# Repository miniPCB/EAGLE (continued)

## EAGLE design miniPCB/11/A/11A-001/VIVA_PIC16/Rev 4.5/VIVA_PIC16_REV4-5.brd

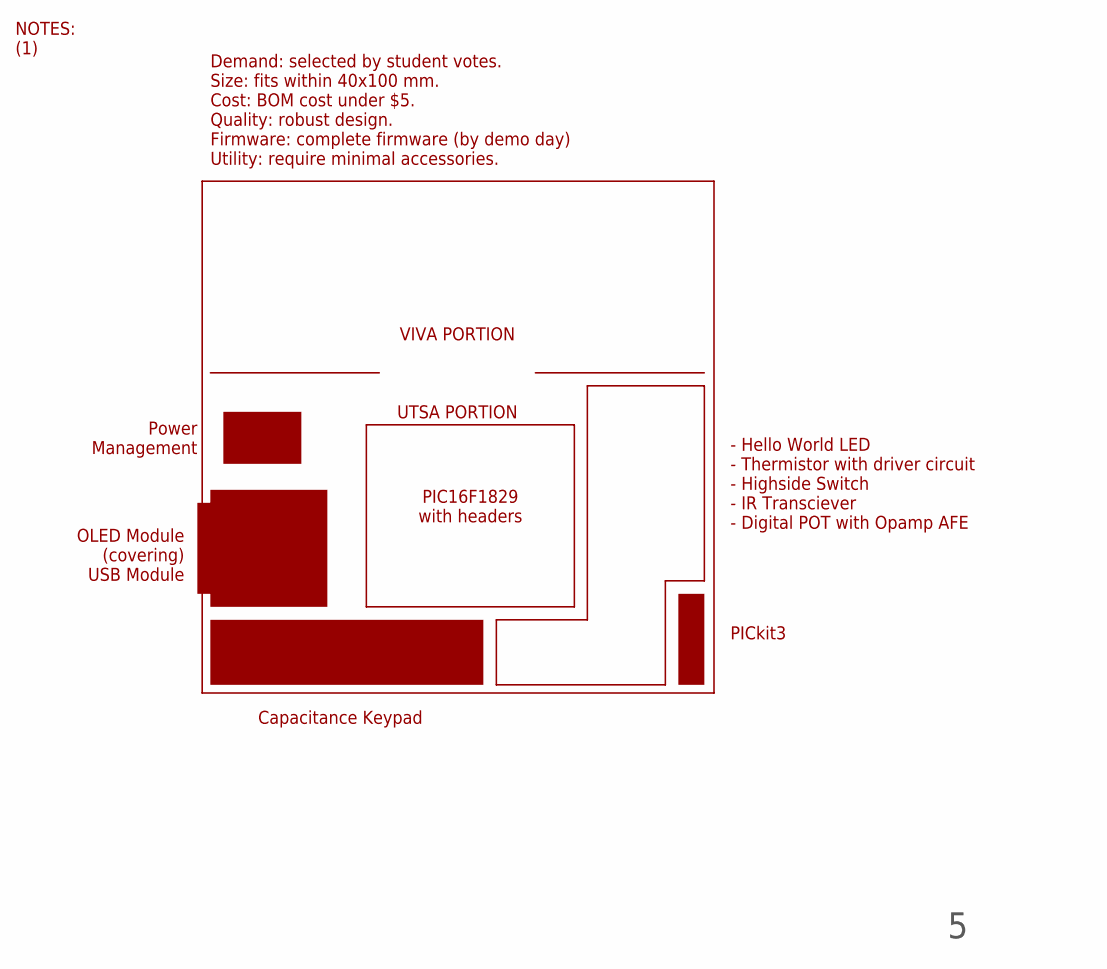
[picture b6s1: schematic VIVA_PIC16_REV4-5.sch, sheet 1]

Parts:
U$1: VIVA_LOGO

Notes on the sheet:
NOTES: (1)
UTSA PORTION
VIVA PORTION
Demand: selected by student votes. Size: fits within 40x100 mm. Cost: BOM cost under $5. Quality: robust design. Firmware: complete firmware (by demo day) Utility: require minimal accessories.
OLED Module (covering) USB Module
Power Management
Capacitance Keypad
PICkit3
PIC16F1829 with headers
- Hello World LED - Thermistor with driver circuit - Highside Switch - IR Transciever - Digital POT with Opamp AFE

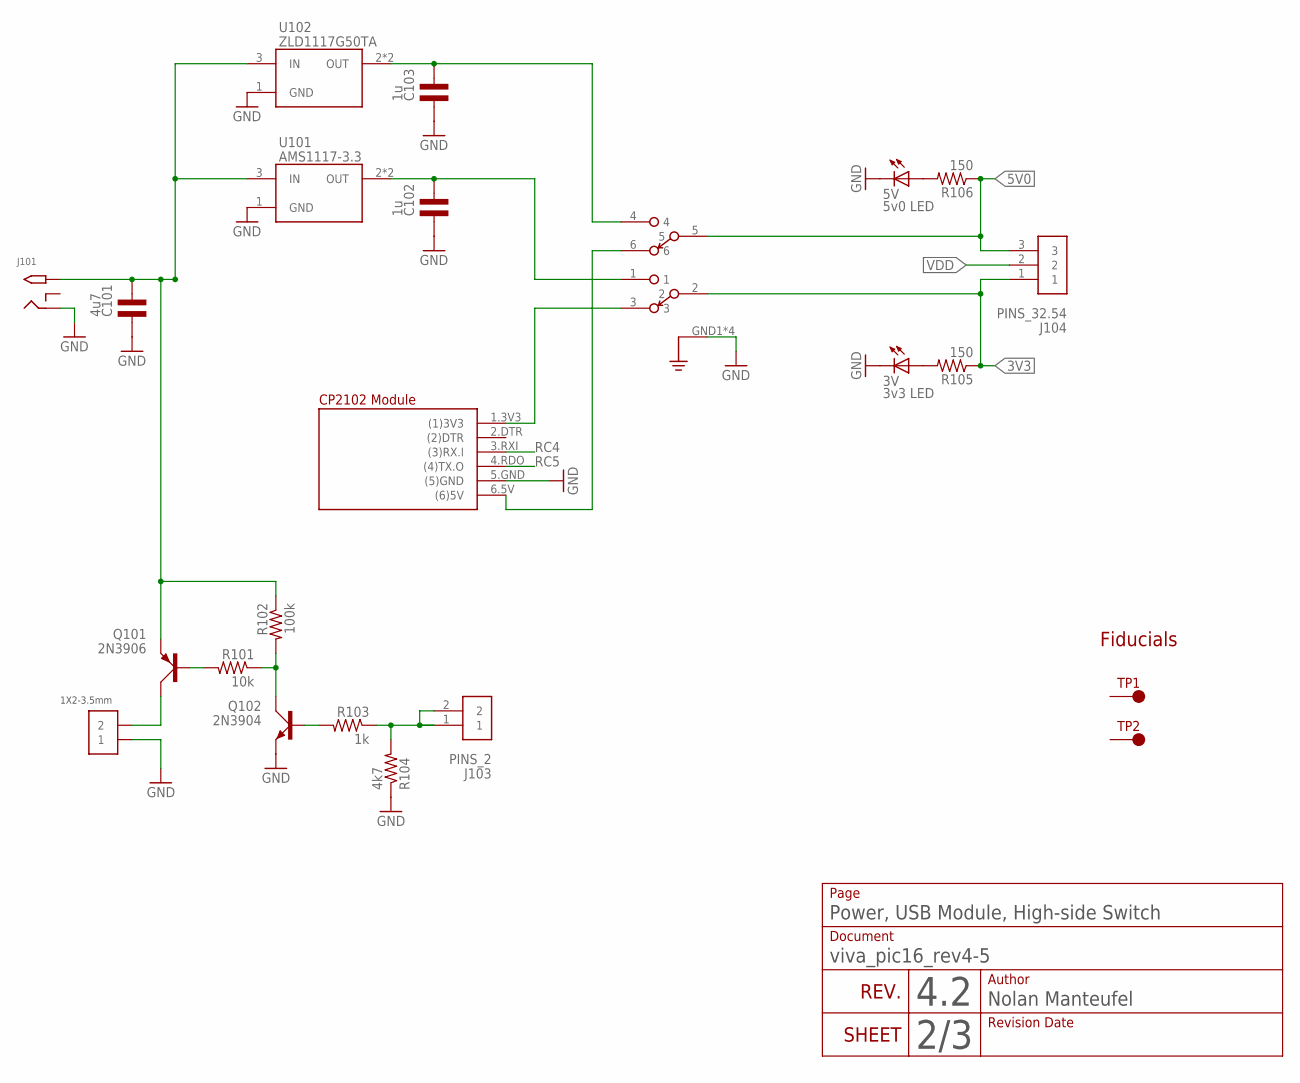
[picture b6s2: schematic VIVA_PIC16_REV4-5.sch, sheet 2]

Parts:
3V: 3v3 LED; CHIPLED_0805
5V: 5v0 LED; CHIPLED_0805
C101: 4u7; C0805
C102, C103: 1u; C0805
J101: 2.1MMJACKTHM; PJ-102A
J102: 1X2-3.5MM-3.5MM; 1X2-3.5MM
J103: PINS_2
J104: PINS_32.54; PINS_3
M101: VIVA_USB-TTL; VIVA_USB_TTL_SUBTEXT
Q101: 2N3906; SOT23
Q102: 2N3904; SOT23
R101: 10k; R0805
R102: 100k; R0805
R103: 1k; R0805
R104: 4k7; R0805
R105, R106: 150; R0805
S101: SWITCH_OS202013; OS202013MT5QN1
TP1, TP2: TESTPOINTFIDUCIAL; FIDUCIAL
U101: AMS1117-3.3; SOT223
U102: ZLD1117G50TA; SOT223

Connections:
3V3: J104.1, R105.1, S101.2
5V0: J104.3, R106.1, S101.5
GND: 3V.C, 5V.C, C101.1, C102.1, C103.1, J101.RING, J102.1, M101.5.GND ((5)GND), Q102.2 (E), R104.1, S101.GND1 (GND), S101.GND2 (GND), S101.GND3 (GND), S101.GND4 (GND), U101.1 (GND), U102.1 (GND); also elsewhere on the board
unnamed: J103.1, J103.2, R103.1, R104.2
unnamed: 5V.A, R106.2
unnamed: Q101.1 (B), R101.2
unnamed: Q102.3 (C), R101.1, R102.2
unnamed: Q102.1 (B), R103.2
unnamed: M101.1.3V3 ((1)3V3), S101.3
unnamed: J102.2, Q101.3 (C)
unnamed: M101.6.5V ((6)5V), S101.6
unnamed: C103.2, S101.4, U102.2 (OUT), U102.4.TAB (OUT)
unnamed: C102.2, S101.1, U101.2 (OUT), U101.4.TAB (OUT)
unnamed: 3V.A, R105.2
RC4: M101.3.RXI ((3)RX.I); also elsewhere on the board
RC5: M101.4.RDO ((4)TX.O); also elsewhere on the board
VDC: C101.2, J101.TIP, Q101.2 (E), R102.1, U101.3 (IN), U102.3 (IN)
VDD: J104.2; also elsewhere on the board

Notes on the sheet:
REV.
4.2
Revision Date
Author
SHEET
Document
Power, USB Module, High-side Switch
Page
Nolan Manteufel
Fiducials

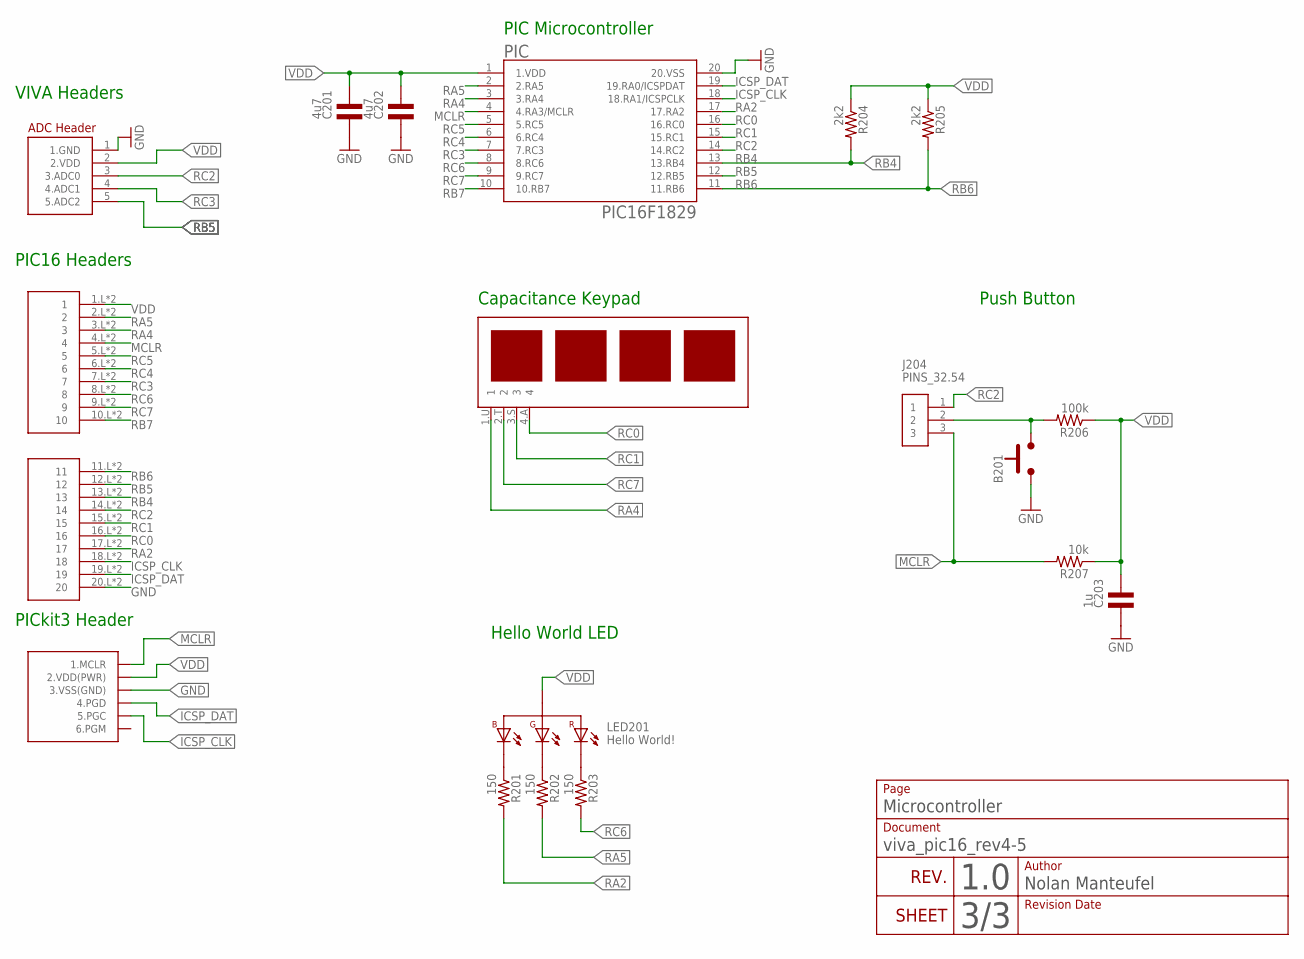
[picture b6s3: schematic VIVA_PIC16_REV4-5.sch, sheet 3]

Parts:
B201: PUSHBUTTON6X6MM; 6X6MM
C201, C202: 4u7; C0805
C203: 1u; C0805
J201: VIVA_PIC16
J202: VIVA-HEADER-ADCNONAME; VIVA-HEADER-ADC-NONAME
J203: PICKIT3
J204: PINS_32.54; PINS_3
LED201: Hello World!; LED_RGB-5050
PIC: PIC16F1829; SOP20-NEW
R201, R202, R203: 150; R0805
R204, R205: 2k2; R0805
R206: 100k; R0805
R207: 10k; R0805
U$201: VIVA_UTSA-KEYPAD

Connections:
GND: B201.1.A (1), B201.2.A (1), C201.1, C202.1, C203.1, J201.20.L (20), J201.20.R (20), J202.1 (1.GND), J203.3 (3.VSS(GND)), PIC.20 (20.VSS); also elsewhere on the board
ICSP_CLK: J201.18.L (18), J201.18.R (18), J203.5 (5.PGC), PIC.18 (18.RA1/ICSPCLK)
ICSP_DAT: J201.19.L (19), J201.19.R (19), J203.4 (4.PGD), PIC.19 (19.RA0/ICSPDAT)
MCLR: J201.4.L (4), J201.4.R (4), J203.1 (1.MCLR), J204.3, PIC.4 (4.RA3/MCLR), R207.2
unnamed: B201.3.B (2), B201.4.B (2), J204.2, R206.2
unnamed: LED201.4.B-, R201.1
unnamed: LED201.2.G-, R202.1
unnamed: LED201.1.R-, R203.1
RA2: J201.17.L (17), J201.17.R (17), PIC.17 (17.RA2), R201.2
RA4: J201.3.L (3), J201.3.R (3), PIC.3 (3.RA4), U$201.1.U (1)
RA5: J201.2.L (2), J201.2.R (2), PIC.2 (2.RA5), R202.2
RB4: J201.13.L (13), J201.13.R (13), PIC.13 (13.RB4), R204.2
RB5: J201.12.L (12), J201.12.R (12), J202.5 (5.ADC2), PIC.12 (12.RB5)
RB6: J201.11.L (11), J201.11.R (11), PIC.11 (11.RB6), R205.2
RB7: J201.10.L (10), J201.10.R (10), PIC.10 (10.RB7)
RC0: J201.16.L (16), J201.16.R (16), PIC.16 (16.RC0), U$201.4.A (4)
RC1: J201.15.L (15), J201.15.R (15), PIC.15 (15.RC1), U$201.3.S (3)
RC2: J201.14.L (14), J201.14.R (14), J202.3 (3.ADC0), J204.1, PIC.14 (14.RC2)
RC3: J201.7.L (7), J201.7.R (7), J202.4 (4.ADC1), PIC.7 (7.RC3)
RC4: J201.6.L (6), J201.6.R (6), PIC.6 (6.RC4); also elsewhere on the board
RC5: J201.5.L (5), J201.5.R (5), PIC.5 (5.RC5); also elsewhere on the board
RC6: J201.8.L (8), J201.8.R (8), PIC.8 (8.RC6), R203.2
RC7: J201.9.L (9), J201.9.R (9), PIC.9 (9.RC7), U$201.2.T (2)
VDD: C201.2, C202.2, C203.2, J201.1.L (1), J201.1.R (1), J202.2 (2.VDD), J203.2 (2.VDD(PWR)), LED201.3.+, PIC.1 (1.VDD), R204.1, R205.1, R206.1, R207.1; also elsewhere on the board

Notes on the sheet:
REV.
1.0
Revision Date
Author
SHEET
Document
Microcontroller
Page
Nolan Manteufel
Push Button
Hello World LED
PICkit3 Header
PIC Microcontroller
VIVA Headers
PIC16 Headers
Capacitance Keypad

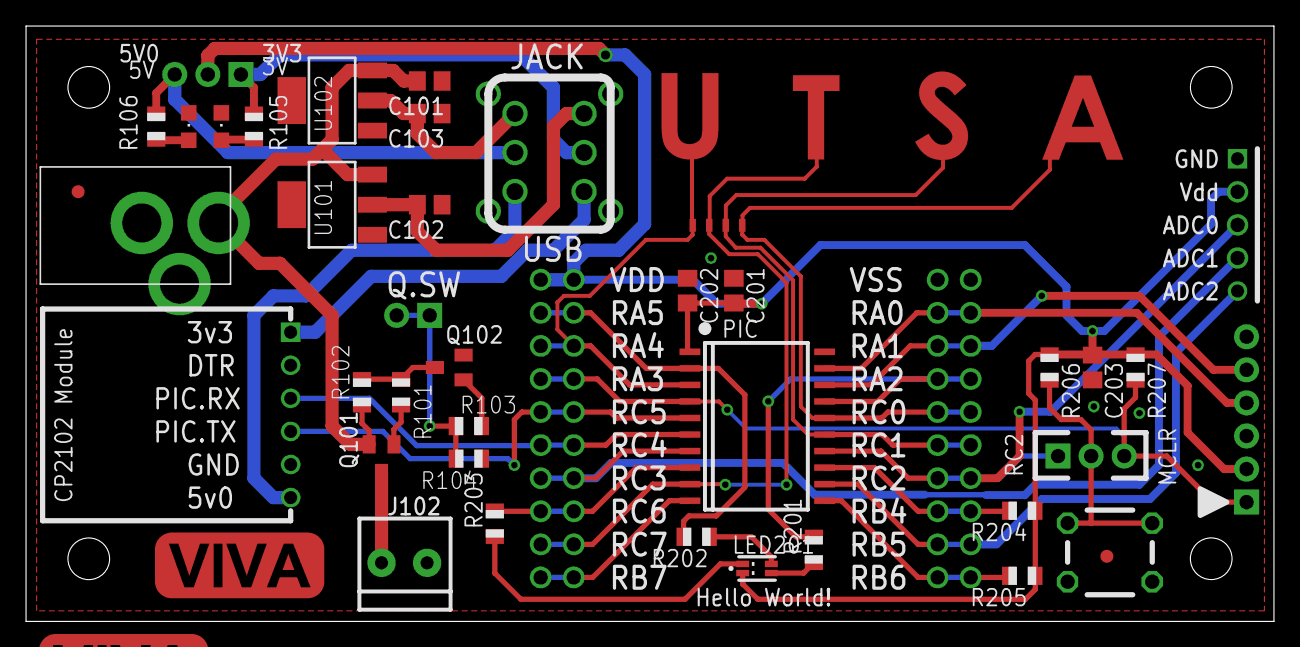
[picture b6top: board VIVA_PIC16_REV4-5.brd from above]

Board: 2 copper layers, 95.8 x 45.7 mm, 43 parts (0 on the bottom side), 38 nets.

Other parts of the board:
U$2: VIVA_LOGO

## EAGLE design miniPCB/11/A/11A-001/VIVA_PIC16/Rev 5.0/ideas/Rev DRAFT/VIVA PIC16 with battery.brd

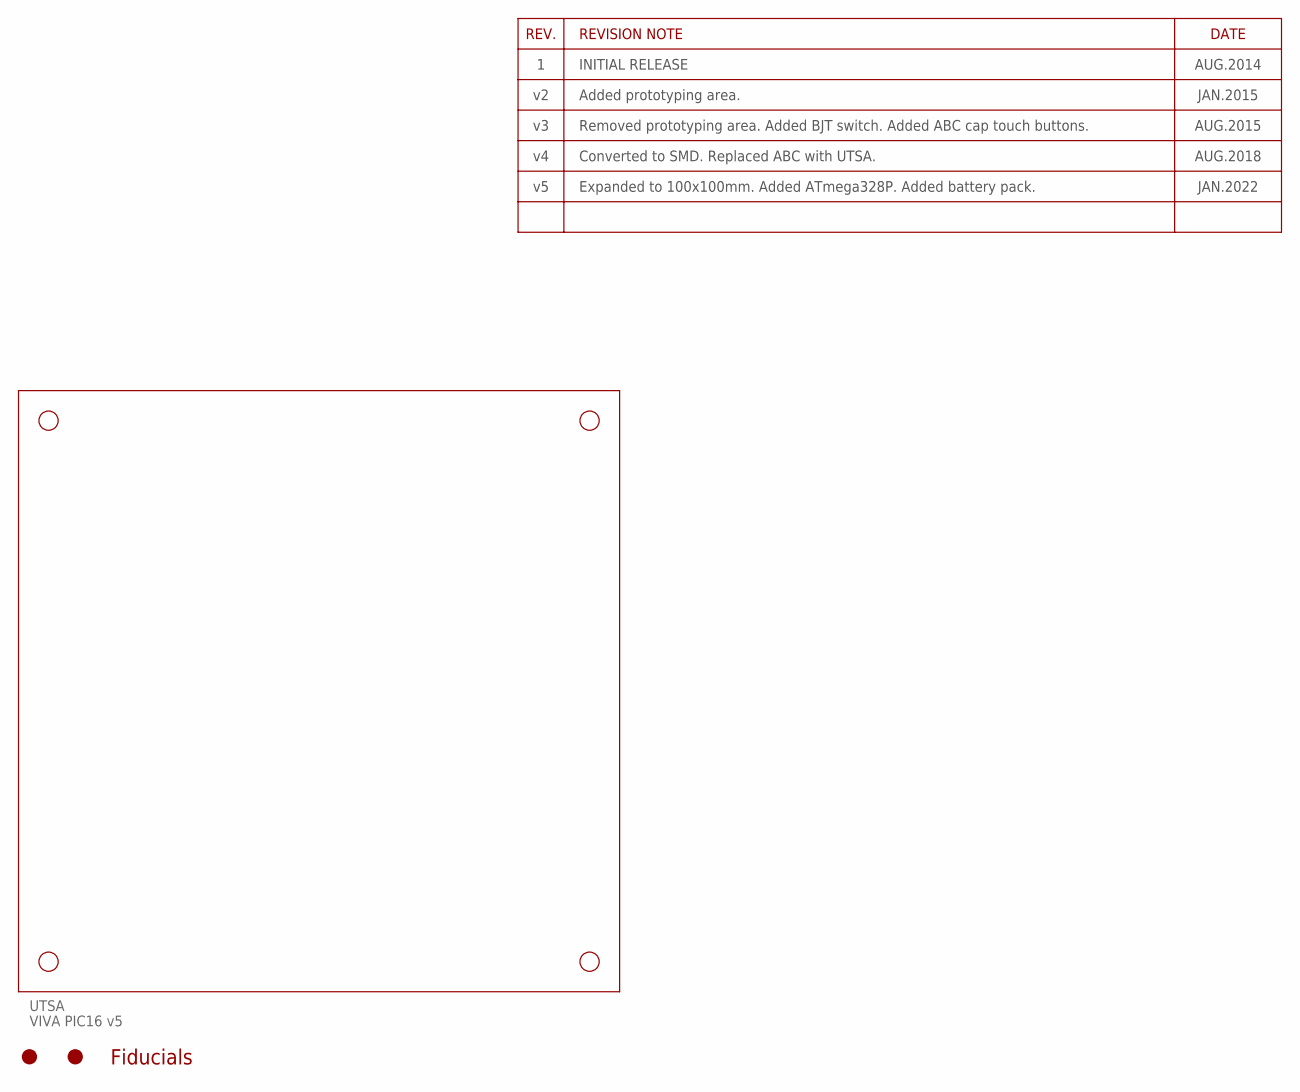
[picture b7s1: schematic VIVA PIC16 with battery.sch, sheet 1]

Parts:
FIDUCIAL1, FIDUCIAL2: FIDUCIAL
UTSA: VIVA PIC16 v5; PCB_100X100

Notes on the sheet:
Fiducials

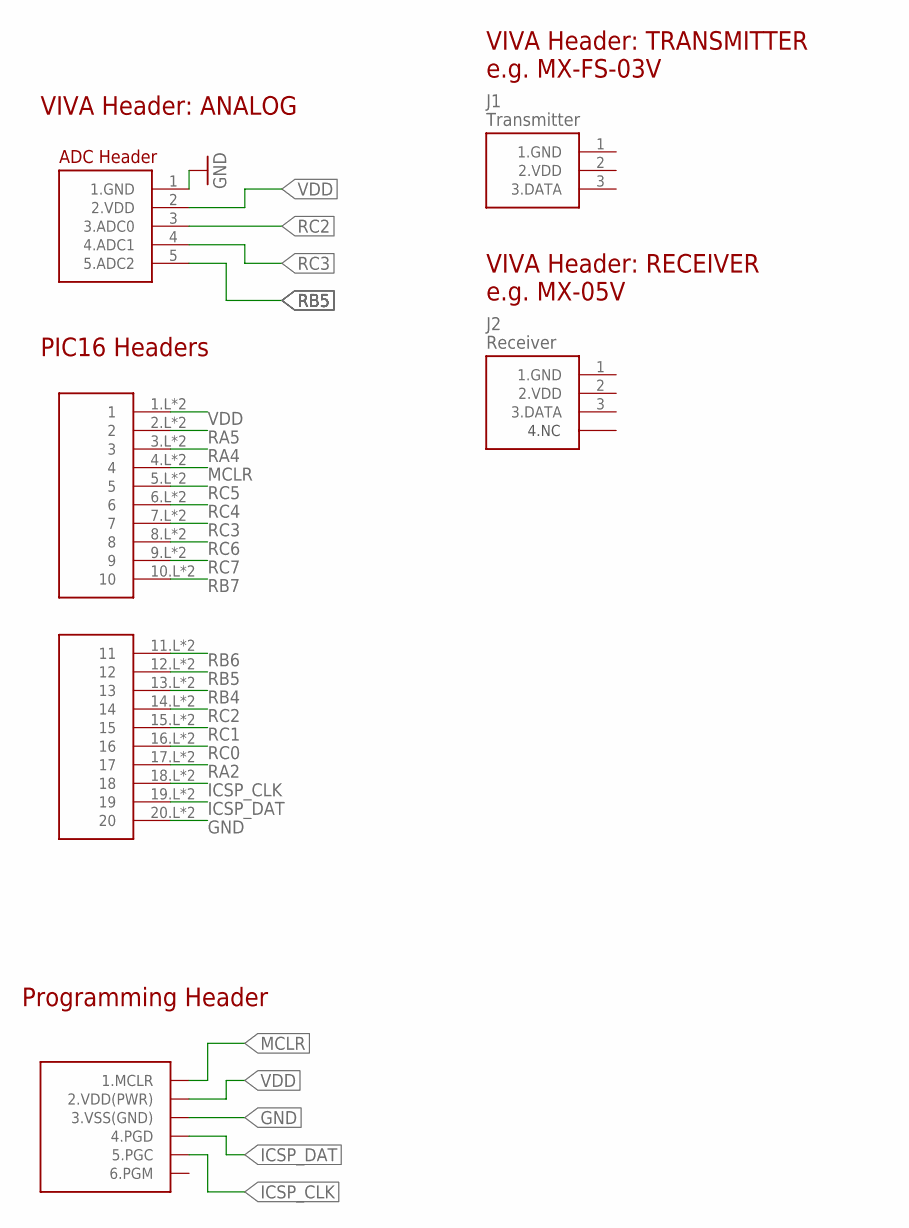
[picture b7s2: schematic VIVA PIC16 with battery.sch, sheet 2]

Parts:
J1: Transmitter; VIVA-HEADER-GPIO-RA-1
J2: Receiver; VIVA-HEADER-RF-RX
J202: VIVA-HEADER-ADCNONAME; VIVA-HEADER-ADC-NONAME
J203: PICKIT3
U$6: VIVA_PIC16BOARD; VIVA_PIC16

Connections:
GND: J202.1 (1.GND), J203.3 (3.VSS(GND)), U$6.20.L (20), U$6.20.R (20); also elsewhere on the board
ICSP_CLK: J203.5 (5.PGC), U$6.18.L (18), U$6.18.R (18); also elsewhere on the board
ICSP_DAT: J203.4 (4.PGD), U$6.19.L (19), U$6.19.R (19); also elsewhere on the board
MCLR: J203.1 (1.MCLR), U$6.4.L (4), U$6.4.R (4); also elsewhere on the board
RA2: U$6.17.L (17), U$6.17.R (17); also elsewhere on the board
RA4: U$6.3.L (3), U$6.3.R (3); also elsewhere on the board
RA5: U$6.2.L (2), U$6.2.R (2); also elsewhere on the board
RB4: U$6.13.L (13), U$6.13.R (13); also elsewhere on the board
RB5: J202.5 (5.ADC2), U$6.12.L (12), U$6.12.R (12); also elsewhere on the board
RB6: U$6.11.L (11), U$6.11.R (11); also elsewhere on the board
RB7: U$6.10.L (10), U$6.10.R (10); also elsewhere on the board
RC0: U$6.16.L (16), U$6.16.R (16); also elsewhere on the board
RC1: U$6.15.L (15), U$6.15.R (15); also elsewhere on the board
RC2: J202.3 (3.ADC0), U$6.14.L (14), U$6.14.R (14); also elsewhere on the board
RC3: J202.4 (4.ADC1), U$6.7.L (7), U$6.7.R (7); also elsewhere on the board
RC4: U$6.6.L (6), U$6.6.R (6); also elsewhere on the board
RC5: U$6.5.L (5), U$6.5.R (5); also elsewhere on the board
RC6: U$6.8.L (8), U$6.8.R (8); also elsewhere on the board
RC7: U$6.9.L (9), U$6.9.R (9); also elsewhere on the board
VDD: J202.2 (2.VDD), J203.2 (2.VDD(PWR)), U$6.1.L (1), U$6.1.R (1); also elsewhere on the board

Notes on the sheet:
VIVA Header: ANALOG
PIC16 Headers
VIVA Header: TRANSMITTER e.g. MX-FS-03V
VIVA Header: RECEIVER e.g. MX-05V
Programming Header

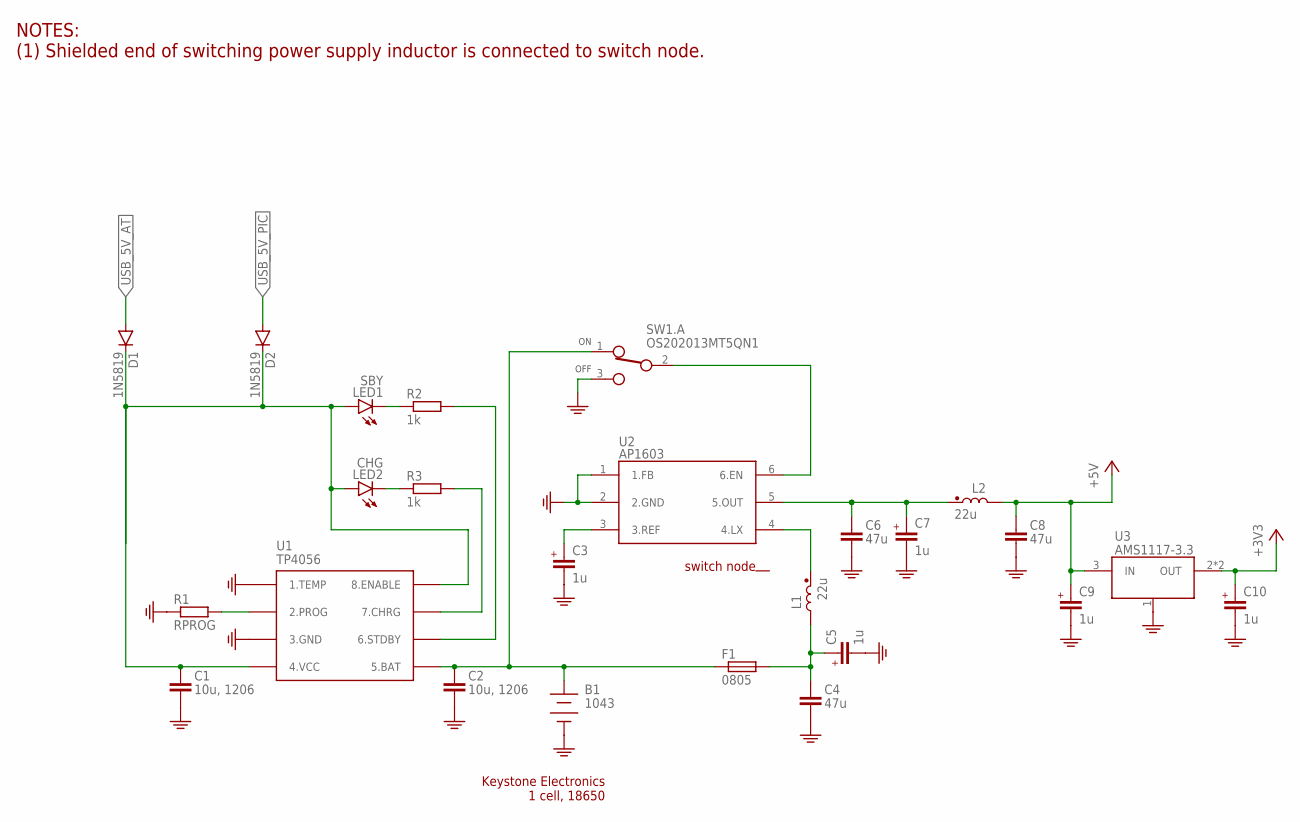
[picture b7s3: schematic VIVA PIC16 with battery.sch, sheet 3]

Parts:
B1: 1043; BATTERY-18650-1
C1, C2: 10u, 1206; C1206
C3, C5, C7, C9, C10: 1u; C0805
C4, C6, C8: 47u; C-WE-5MM
D1, D2: 1N5819; SOD80C
F1: 0805; F0805
L1, L2: 22u; SRN5040
LED1: SBY; CHIPLED_0603
LED2: CHG; CHIPLED_0603
R1: RPROG; R0805
R2, R3: 1k; R0805
SW1.: OS202013MT5QN1
U1: TP4056; SO08-THERMAL
U2: AP1603; SOT23-6
U3: AMS1117-3.3; SOT223

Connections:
+3V3: C10.2 (+), U3.2 (OUT), U3.4.TAB (OUT)
+5V: C8.1+ (1), C9.2 (+), L2.1, U3.3 (IN)
B+: B1.+, C2.+ (1), F1.1, SW1..1 (ON), U1.5 (5.BAT)
B+_FUSED: C4.1+ (1), C5.2 (+), F1.2, L1.1
CHARGE: R3.2, U1.7 (7.CHRG)
DCDC_ENABLE: SW1..2 (IN), U2.6 (6.EN)
DCDC_OUT: C6.1+ (1), C7.2 (+), L2.2, U2.5 (5.OUT)
DCDC_REF: C3.2 (+), U2.3 (3.REF)
GND: B1.1 (-), C1.- (2), C2.- (2), C3.1 (-), C4.2- (2), C5.1 (-), C6.2- (2), C7.1 (-), C8.2- (2), C9.1 (-), C10.1 (-), R1.1, SW1..3 (OFF), U1.1 (1.TEMP), U1.3 (3.GND), U1.THERMAL (3.GND), U2.1 (1.FB), U2.2 (2.GND), U3.1 (GND); also elsewhere on the board
unnamed: LED1.C, R2.1
unnamed: LED2.C, R3.1
unnamed: R1.2, U1.2 (2.PROG)
STANDBY: R2.2, U1.6 (6.STDBY)
SWITCH_NODE: L1.2, U2.4 (4.LX)
USB_5V_AT: D1.A
USB_5V_PIC: D2.A
VCC: C1.+ (1), D1.C, D2.C, LED1.A, LED2.A, U1.4 (4.VCC), U1.8 (8.ENABLE)

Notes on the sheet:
Keystone Electronics 1 cell, 18650
NOTES: (1) Shielded end of switching power supply inductor is connected to switch node.
switch node

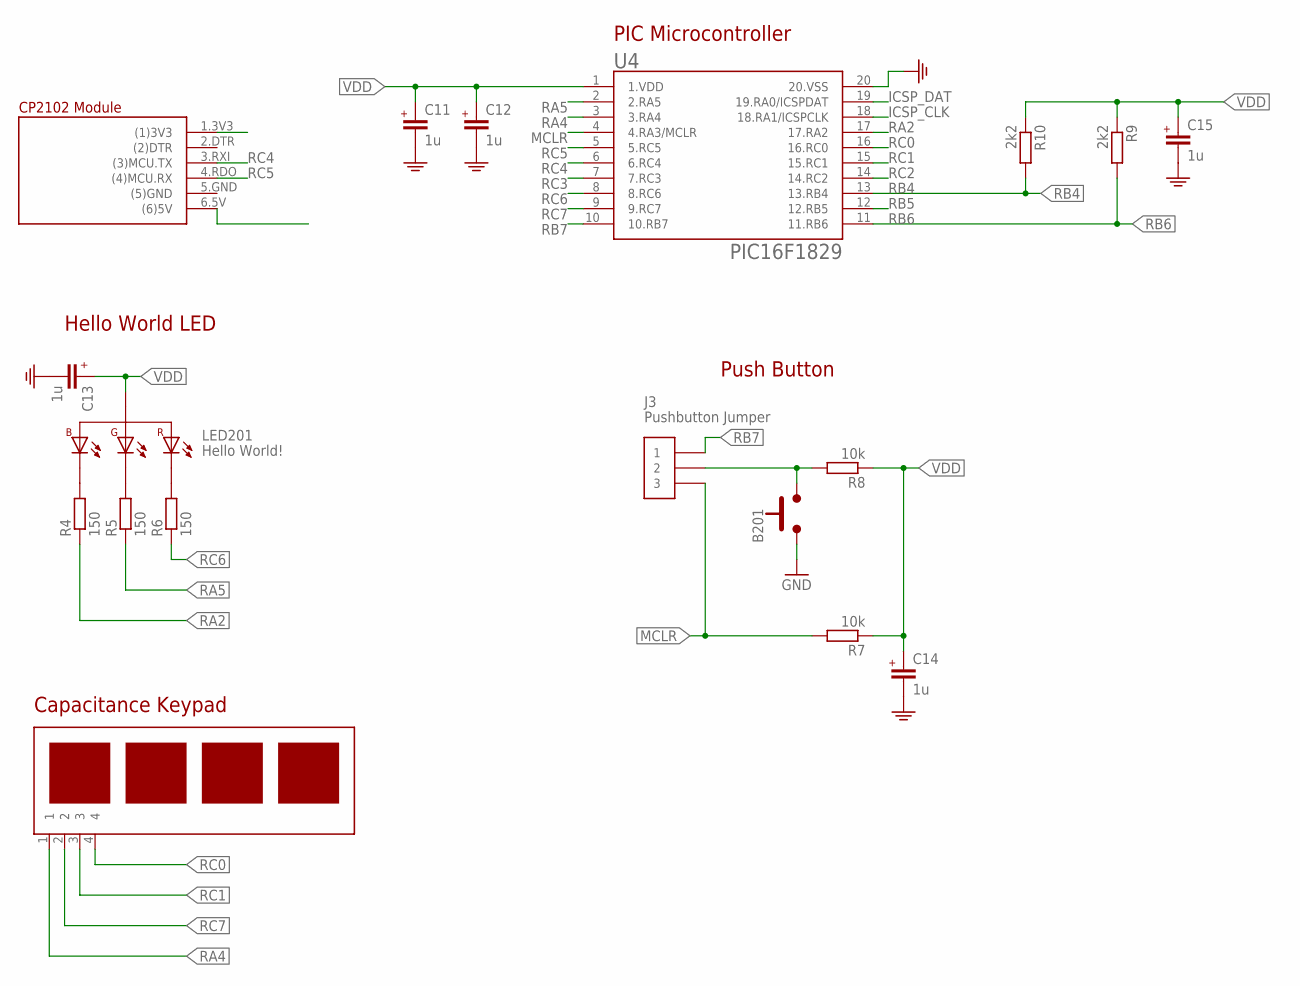
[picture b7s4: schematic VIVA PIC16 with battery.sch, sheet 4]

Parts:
B201: PUSHBUTTON6X6MM; 6X6MM
C11, C12, C13, C14, C15: 1u; C0805
J3: Pushbutton Jumper; PINS_3
LED201: Hello World!; LED_RGB-5050
R4, R5, R6: 150; R0805
R7, R8: 10k; R0805
R9, R10: 2k2; R0805
U4: PIC16F1829; SOP20-NEW
U$7: VIVA_UTSA-KEYPADV5; VIVA_UTSA-KEYPAD-V5
U$11: VIVA_USB-TTL; VIVA_USB_TTL_SUBTEXT

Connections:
GND: B201.1.A (1), B201.2.A (1), C11.1 (-), C12.1 (-), C13.1 (-), C14.1 (-), C15.1 (-), U4.20 (20.VSS); also elsewhere on the board
ICSP_CLK: U4.18 (18.RA1/ICSPCLK); also elsewhere on the board
ICSP_DAT: U4.19 (19.RA0/ICSPDAT); also elsewhere on the board
MCLR: J3.3, R7.2, U4.4 (4.RA3/MCLR); also elsewhere on the board
unnamed: B201.3.B (2), B201.4.B (2), J3.2, R8.2
unnamed: LED201.2.G-, R5.2
unnamed: LED201.1.R-, R6.2
unnamed: LED201.4.B-, R4.2
RA2: R4.1, U4.17 (17.RA2); also elsewhere on the board
RA4: U4.3 (3.RA4), U$7.1; also elsewhere on the board
RA5: R5.1, U4.2 (2.RA5); also elsewhere on the board
RB4: R10.2, U4.13 (13.RB4); also elsewhere on the board
RB5: U4.12 (12.RB5); also elsewhere on the board
RB6: R9.2, U4.11 (11.RB6); also elsewhere on the board
RB7: J3.1, U4.10 (10.RB7); also elsewhere on the board
RC0: U4.16 (16.RC0), U$7.4; also elsewhere on the board
RC1: U4.15 (15.RC1), U$7.3; also elsewhere on the board
RC2: U4.14 (14.RC2); also elsewhere on the board
RC3: U4.7 (7.RC3); also elsewhere on the board
RC4: U4.6 (6.RC4), U$11.3.RXI ((3)MCU.TX); also elsewhere on the board
RC5: U4.5 (5.RC5), U$11.4.RDO ((4)MCU.RX); also elsewhere on the board
RC6: R6.1, U4.8 (8.RC6); also elsewhere on the board
RC7: U4.9 (9.RC7), U$7.2; also elsewhere on the board
VDD: C11.2 (+), C12.2 (+), C13.2 (+), C14.2 (+), C15.2 (+), LED201.3.+, R7.1, R8.1, R9.1, R10.1, U4.1 (1.VDD); also elsewhere on the board

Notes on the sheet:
Push Button
Hello World LED
PIC Microcontroller
Capacitance Keypad

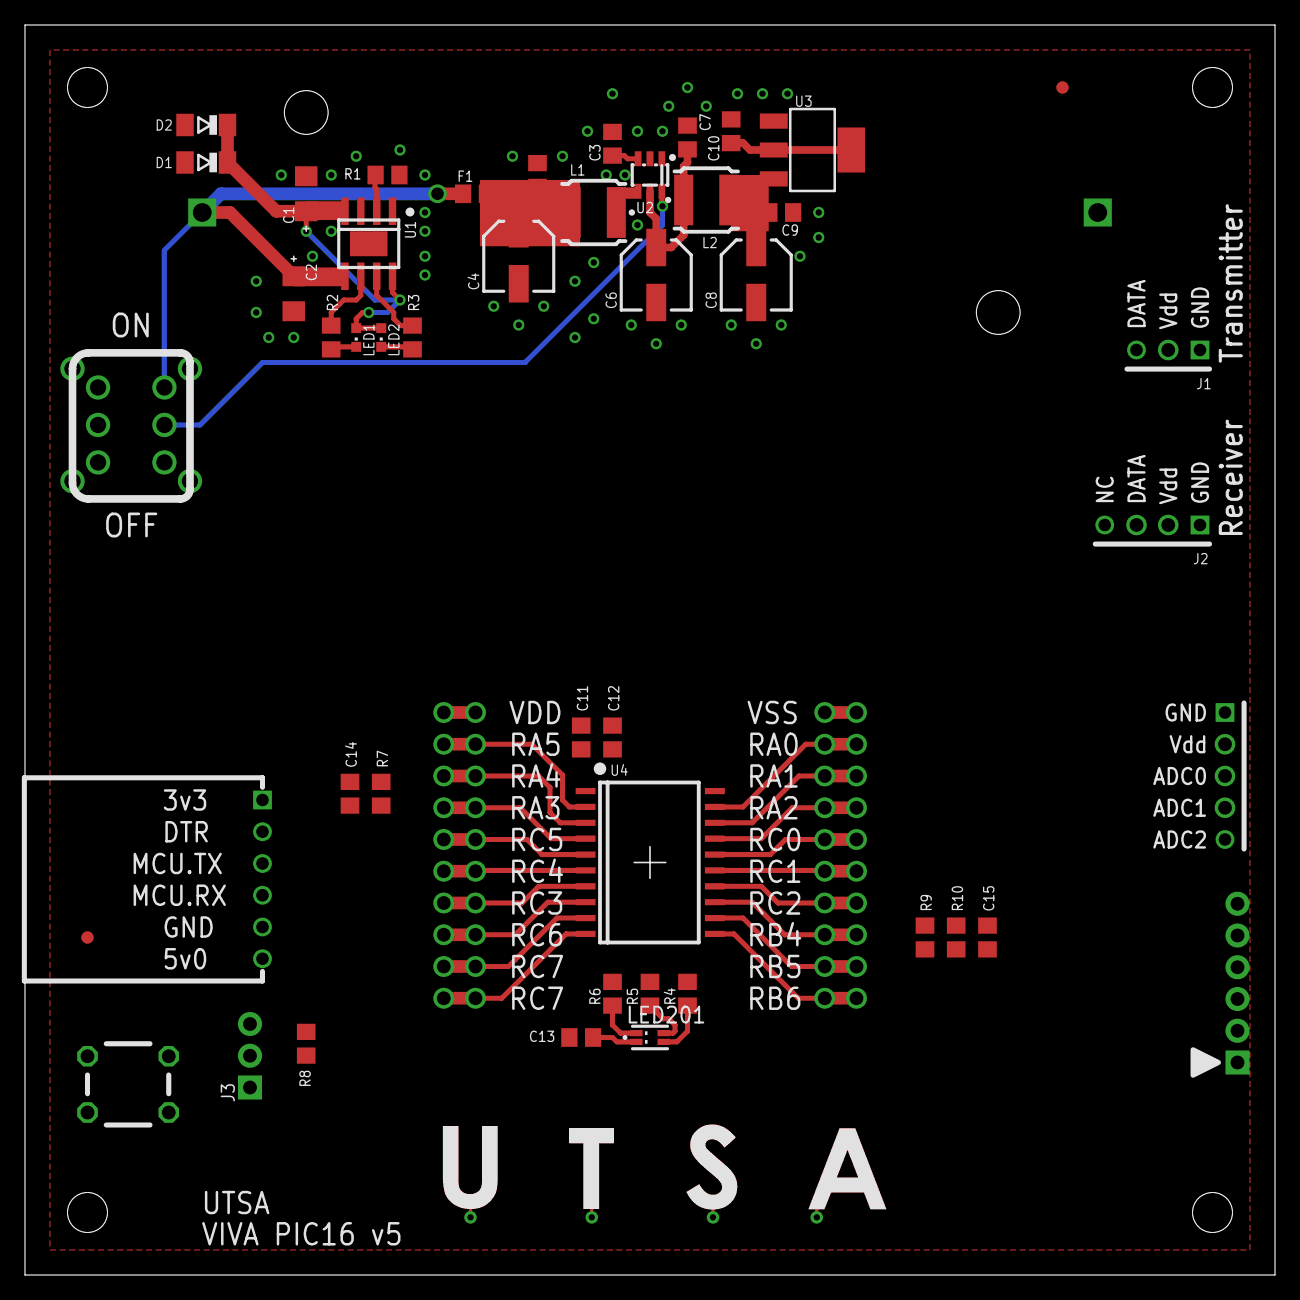
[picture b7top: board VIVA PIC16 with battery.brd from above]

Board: 2 copper layers, 100.0 x 100.0 mm, 51 parts (1 on the bottom side), 38 nets.
